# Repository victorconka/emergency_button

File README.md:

# Emergency Button  
## About  
"emergency button" project based on attiny85, nrf24l01, esp8266 based devboard, telegram and email API's  
  
### Main funcions:  
*     	Attend Telegram Commands.  
*     	Telegram Authorization (access control).  
*     	Listen for the Alert button being pressed.  
*     	Send WOL packet to the PC.  
*     	Send Ping packets to the configured IP Address.  
### Folder contains:  
* UML project files.  
* Enclosure for both, button and server. (opensource, not mine).  
* libraries used to compile arduino files for the server since the compilation is tricky because of the number of libraries used and available SRAM.  
* The code for Arduino IDE.  
* Schematics for the circuits (be aware that some of the part libraries were missing, so same shape parts were used.)  
  
## Configuration  
### Server  
#### Schematic:  
  
#### PCB  
  
### Emergency Button  
#### Schematic  
  
#### PCB Layout  
  
#### PCB Implementation  
##### BACK
  
##### FRONT
  
#### Battery Consumption  
  
## Further Improvements  
### Battery improvement  
Only a step-down voltage regulator is included in the circuit. This means we can use batteries with voltage values up to 6V. Battery voltage will be stepped down to 3.3V, which is the value at which the circuit operates.  
Device uses CR2032 batterie which nominal value is 3V. Once it's charge goes under 2.6V, NRF24L01 is unable to operate properly.  
Adding an additional step up resistor will consume some extra microAmps, but in exchange the battery will get dryed out down to 0.8V.

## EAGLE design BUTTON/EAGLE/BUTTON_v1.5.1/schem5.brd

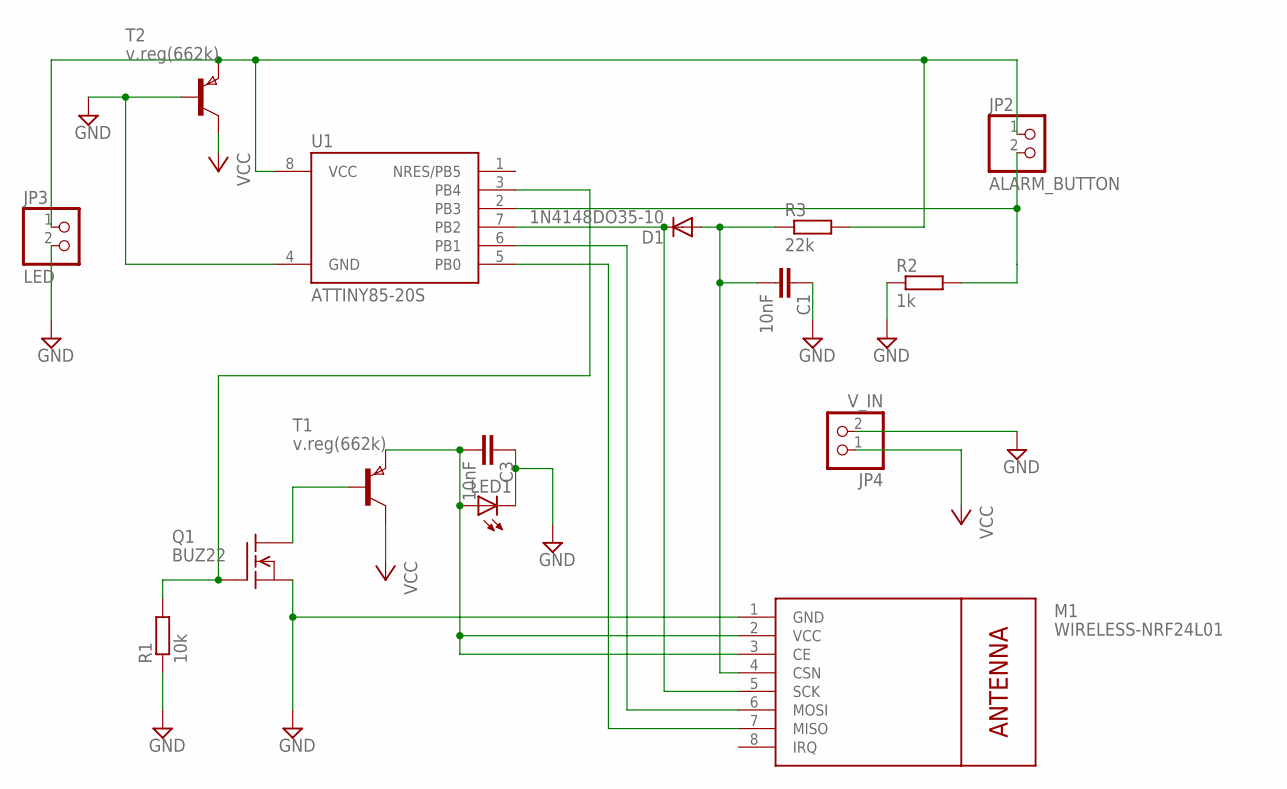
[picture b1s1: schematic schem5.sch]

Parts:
C1, C3: 10nF; C2.5-2
D1: 1N4148DO35-10; DO35-10
JP2: ALARM_BUTTON; 1X02
JP3: LED; 1X02
JP4: V_IN; 1X02
LED1: LED5MM
M1: WIRELESS-NRF24L01
Q1: BUZ22; TO220
R1: 10k; 0204/7
R2: 1k; 0204/7
R3: 22k; 0204/7
T1, T2: v.reg(662k); SOT323
U1: ATTINY85-20S; SOIC8_EIAJ_208MIL

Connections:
GND: C1.1, C3.1, JP3.2, JP4.2, LED1.K (C), M1.1 (GND), Q1.3 (S), R1.1, R2.1, T2.2 (B), U1.4 (GND)
unnamed: D1.C, M1.5 (SCK), U1.7 (PB2)
unnamed: JP2.2, R2.2, U1.2 (PB3)
unnamed: Q1.1 (G), R1.2, U1.3 (PB4)
unnamed: Q1.2 (D), T1.2 (B)
unnamed: C1.2, D1.A, M1.4 (CSN), R3.1
unnamed: C3.2, LED1.A, M1.2 (VCC), M1.3 (CE), T1.3 (E)
unnamed: M1.6 (MOSI), U1.6 (PB1)
unnamed: M1.7 (MISO), U1.5 (PB0)
VCC: JP4.1, T1.1 (C), T2.1 (C)
VCC1: JP2.1, JP3.1, R3.2, T2.3 (E), U1.8 (VCC)

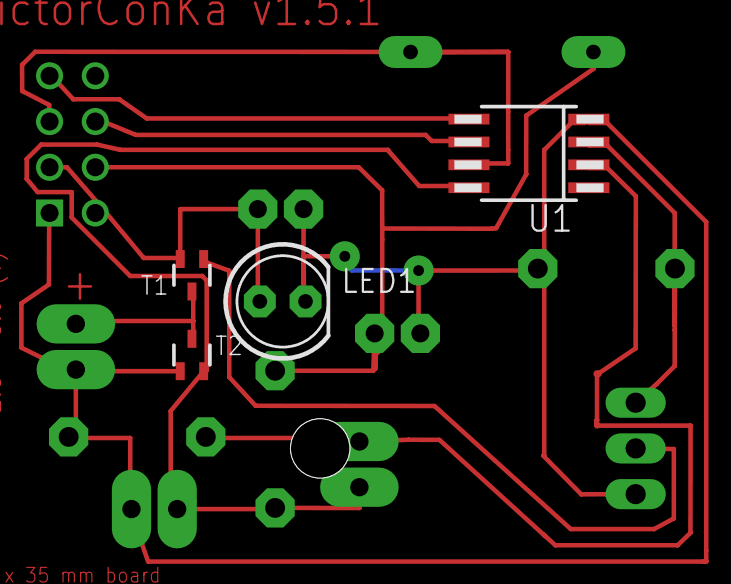
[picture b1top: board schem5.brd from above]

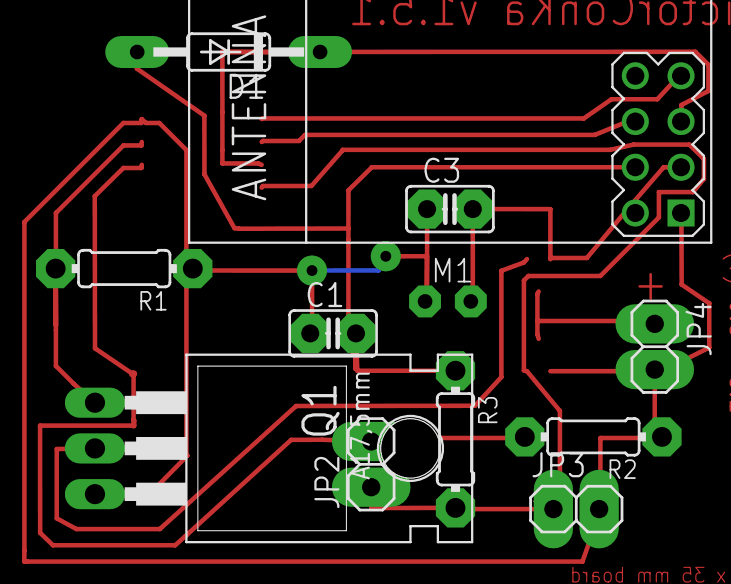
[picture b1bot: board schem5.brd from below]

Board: 2 copper layers, 15 parts (11 on the bottom side), 11 nets.

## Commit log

2017-08-28 button code and schematic
2017-08-28 minor change to avoid counter overflow and attiny hang problem
2017-08-28 typo fix
2017-09-11 button read and toggle once
2017-10-31 working server version and modified button code which was refactored to make it more readable and remove recursion
2017-10-31 server schematic added
2017-10-31 added libraries used for this project
2017-11-08 refactoring some code
2017-11-19 few changes and the script
2017-12-04 some fixes
2017-12-04 some readme files added
2018-02-12 disabled debugging messages for the wifi
2018-02-13 wol destination_ip_address fix
2018-03-10 added image to readme
2018-03-10 added info to readme

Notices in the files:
parts and their libraries:
diy-modules: Released under the Creative Commons Attribution 4.0 International License: http://creativecommons.org/licenses/by/4.0
